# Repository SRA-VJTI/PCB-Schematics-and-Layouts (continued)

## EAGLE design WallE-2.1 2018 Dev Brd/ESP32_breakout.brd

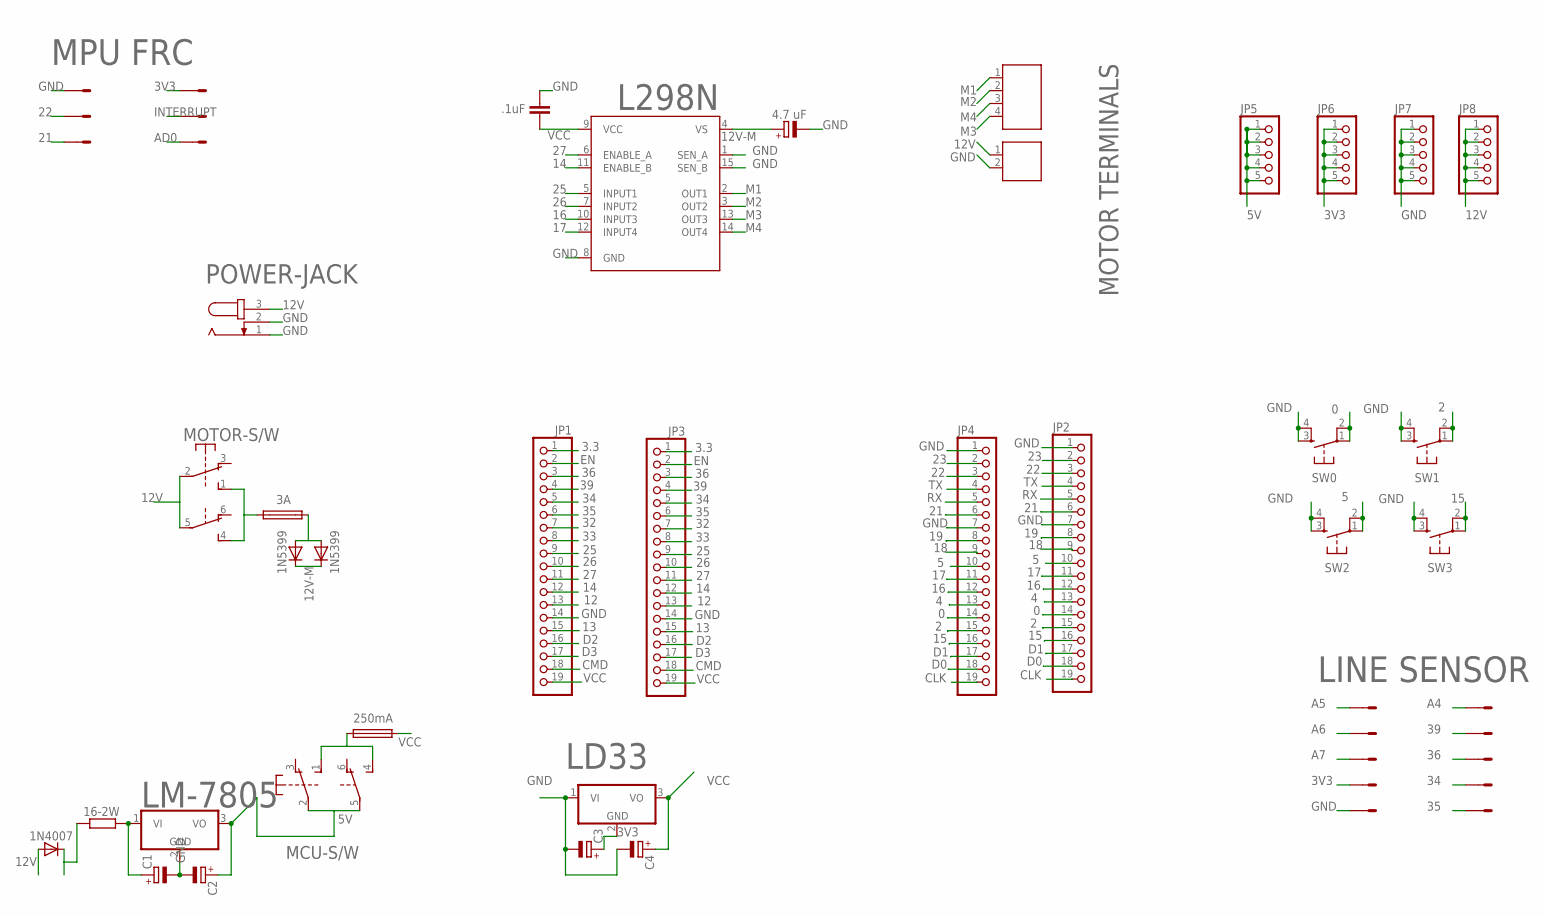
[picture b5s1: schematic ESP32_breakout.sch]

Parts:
12V: 691131710002
16-2W: R-EU_0617/17; 0617/17
C1, C2, C3, C4: CPOL-EUE2.5-6; E2,5-6
C8: 4.7 uF; E2,5-6
C9: .1uF; C5B2.5
D4: 1N4007; D-7.5
D6, D7: 1N5399; DO15-12
F1: 3A; SH25
F2: 250mA; SH25
J1: 691131710004
JP1, JP2, JP3, JP4: PINHD-1X19; 1X19
JP5, JP6, JP7, JP8: PINHD-1X5; 1X05
L298N: L298; MULTIWATT-15
LD33: 786TV; TO220V
LINE-SENSOR: 057-010-1
LM-7805: 786TV; TO220V
MCU-S/W: 9077-2
MOTOR-S/W: 9077-2
MPU-6050: 057-006-1
POWER-JACK: JACK-PLUG1; SPC4078
SW0, SW1, SW2, SW3: DTS-6

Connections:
0: JP2.14, JP4.14, SW0.1, SW0.2
2: JP2.15, JP4.15, SW1.1, SW1.2
3.3: JP1.1, JP3.1
3V3: C3.+, JP6.1, JP6.2, JP6.3, JP6.4, JP6.5, LD33.2 (GND), LINE-SENSOR.7, MPU-6050.2
4: JP2.13, JP4.13
5: JP2.10, JP4.10, SW2.1, SW2.2
5V: C2.+, JP5.1, JP5.2, JP5.3, JP5.4, JP5.5, LM-7805.3 (VO), MCU-S/W.2, MCU-S/W.5
12: JP1.13, JP3.13
12V: 12V.1, D4.A, JP8.1, JP8.2, JP8.3, JP8.4, JP8.5, MOTOR-S/W.2, MOTOR-S/W.5, POWER-JACK.3
12V-M: C8.+, D6.C, D7.C, L298N.4 (VS)
13: JP1.15, JP3.15
14: JP1.12, JP3.12, L298N.11 (ENABLE_B)
15: JP2.16, JP4.16, SW3.1, SW3.2
16: JP2.12, JP4.12, L298N.10 (INPUT3)
17: JP2.11, JP4.11, L298N.12 (INPUT4)
18: JP2.9, JP4.9
19: JP2.8, JP4.8
21: JP2.6, JP4.6, MPU-6050.5
22: JP2.3, JP4.3, MPU-6050.3
23: JP2.2, JP4.2
25: JP1.9, JP3.9, L298N.5 (INPUT1)
26: JP1.10, JP3.10, L298N.7 (INPUT2)
27: JP1.11, JP3.11, L298N.6 (ENABLE_A)
32: JP1.7, JP3.7
33: JP1.8, JP3.8
34: JP1.5, JP3.5, LINE-SENSOR.8
35: JP1.6, JP3.6, LINE-SENSOR.10
36: JP1.3, JP3.3, LINE-SENSOR.6
39: JP1.4, JP3.4, LINE-SENSOR.4
A4: LINE-SENSOR.2
A5: LINE-SENSOR.1
A6: LINE-SENSOR.3
A7: LINE-SENSOR.5
CLK: JP2.19, JP4.19
CMD: JP1.18, JP3.18
D0: JP2.18, JP4.18
D1: JP2.17, JP4.17
D2: JP1.16, JP3.16
D3: JP1.17, JP3.17
EN: JP1.2, JP3.2
GND: 12V.2, C1.-, C2.-, C3.-, C4.-, C8.-, C9.2, JP1.14, JP2.1, JP2.7, JP3.14, JP4.1, JP4.7, JP7.1, JP7.2, JP7.3, JP7.4, JP7.5, L298N.1 (SEN_A), L298N.8 (GND), L298N.15 (SEN_B), LD33.1 (VI), LINE-SENSOR.9, LM-7805.2 (GND), MPU-6050.1, MPU-6050.6, POWER-JACK.1, POWER-JACK.2, SW0.3, SW0.4, SW1.3, SW1.4, SW2.3, SW2.4, SW3.3, SW3.4
INTERRUPT: MPU-6050.4
M1: J1.1, L298N.2 (OUT1)
M2: J1.2, L298N.3 (OUT2)
M3: J1.4, L298N.13 (OUT3)
M4: J1.3, L298N.14 (OUT4)
unnamed: 16-2W.2, C1.+, LM-7805.1 (VI)
unnamed: F1.1, MOTOR-S/W.1 (S), MOTOR-S/W.4 (S)
unnamed: F2.1, MCU-S/W.1 (S), MCU-S/W.4 (S)
unnamed: 16-2W.1, D4.C
unnamed: D6.A, D7.A, F1.2
RX: JP2.5, JP4.5
TX: JP2.4, JP4.4
VCC: C4.+, C9.1, F2.2, JP1.19, JP3.19, L298N.9 (VCC), LD33.3 (VO)

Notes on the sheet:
LINE SENSOR
MOTOR TERMINALS
MPU FRC
AD0

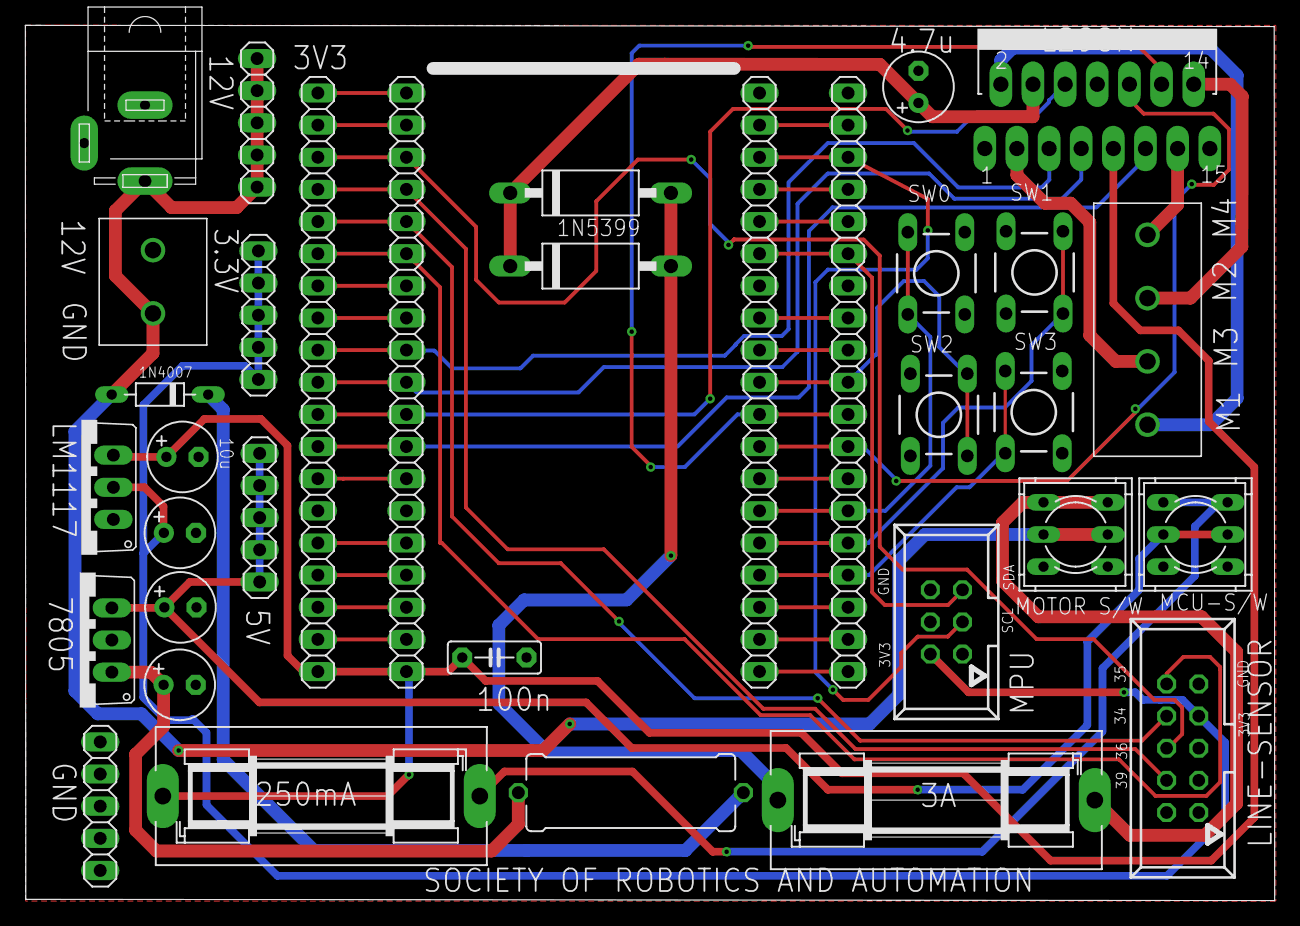
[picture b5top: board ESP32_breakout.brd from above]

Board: 2 copper layers, 98.7 x 69.2 mm, 34 parts (0 on the bottom side), 49 nets.

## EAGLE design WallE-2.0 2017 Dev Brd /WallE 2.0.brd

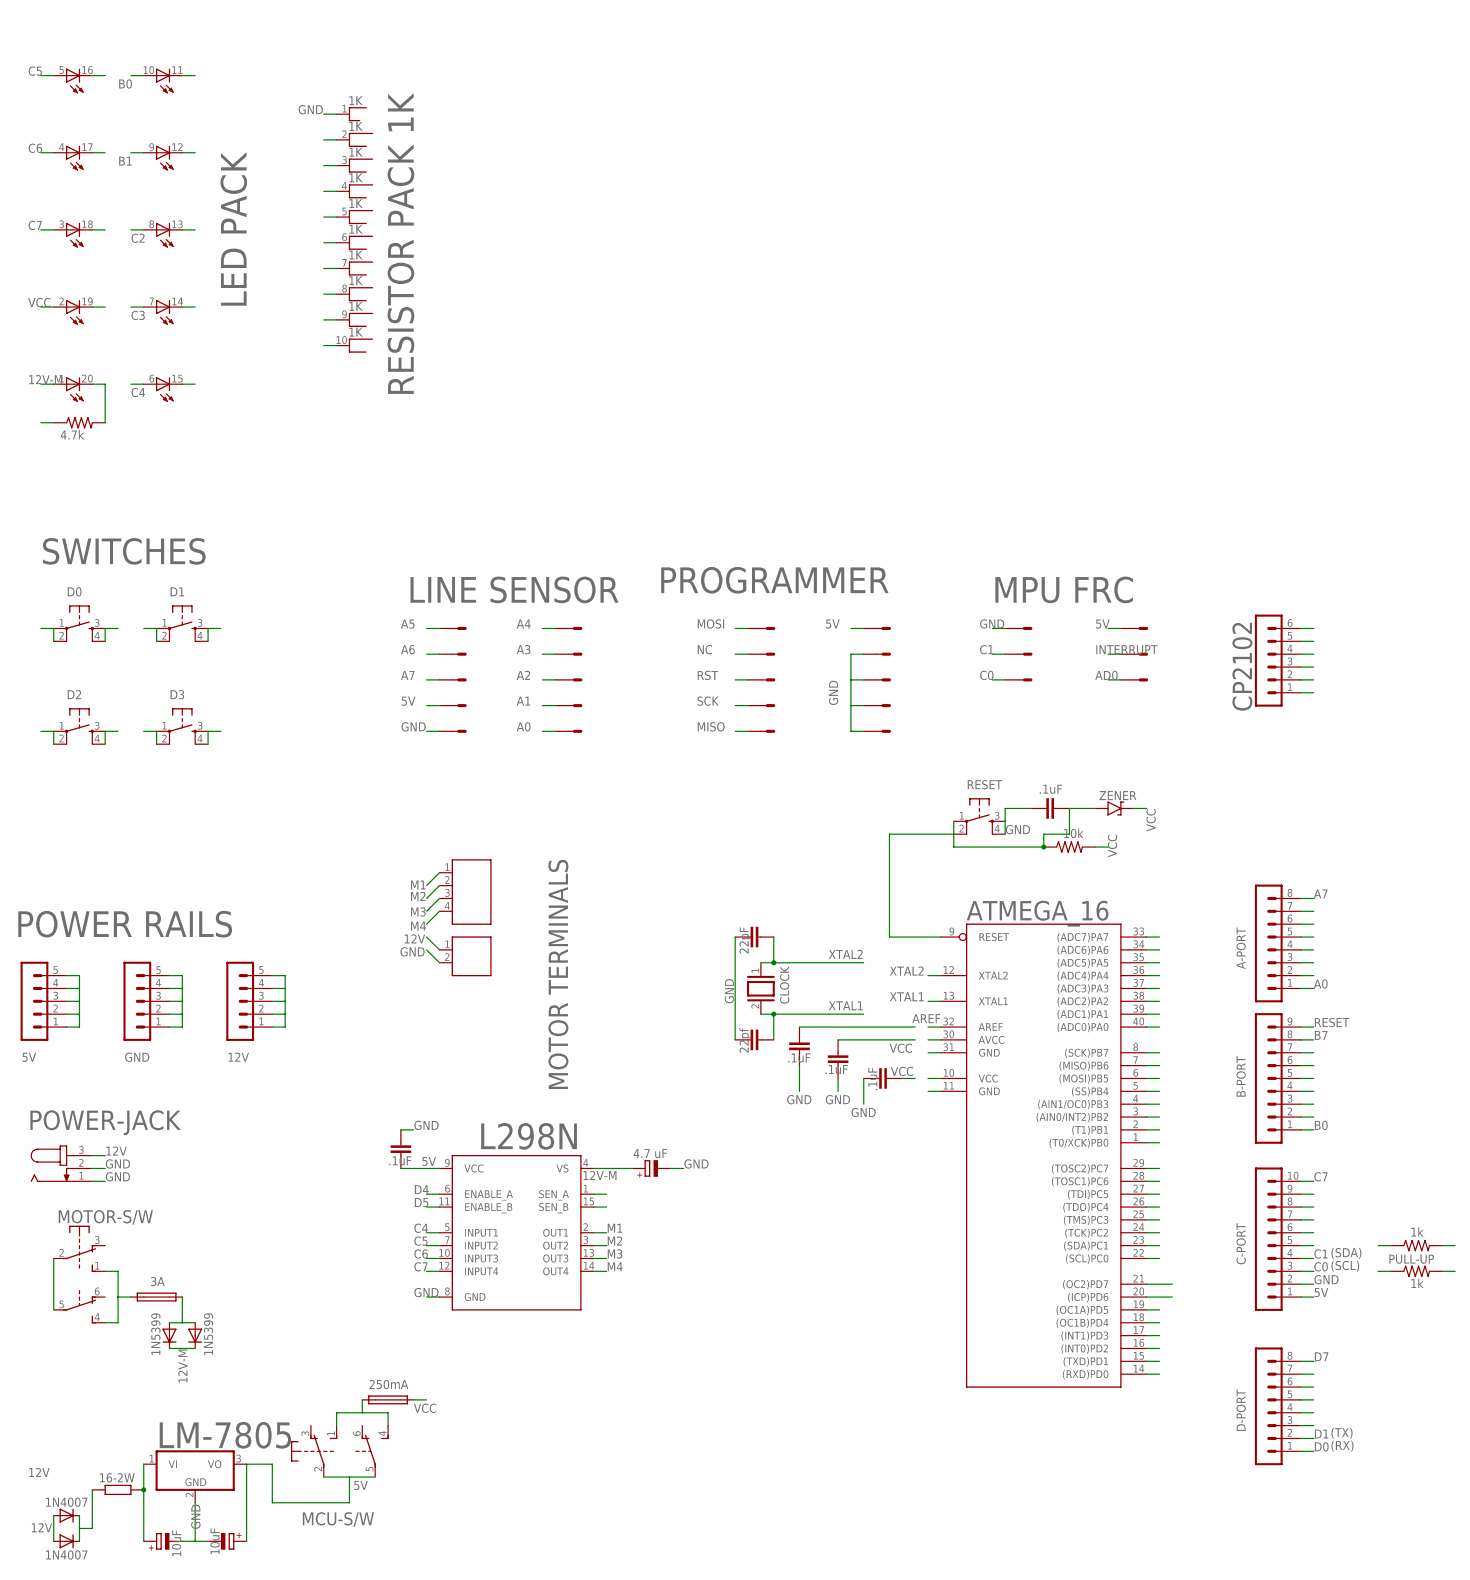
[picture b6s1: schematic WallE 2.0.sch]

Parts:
5V, 12V: MA05-1
16-2W: R-EU_0617/17; 0617/17
A-PORT: MA08-1
ATMEGA_16: MEGA32-P; DIL40
B-PORT: MA09-1
C1, C10: 10uF; E2,5-6
C2, C5, C6, C7, C9: .1uF; C5B2.5
C3: 22pf; C2.5-2
C4: 22pF; C2.5-2
C8: 4.7 uF; E2,5-6
C-PORT: MA10-1
CLOCK: XTAL/S; QS
CP2102: MA06-1
D0, D1, D2, D3: DTS-6
D4, D5: 1N4007; D-7.5
D6, D7: 1N5399; DO15-12
D-PORT: MA08-1
DZ1: LB10
F1: 3A; SH25
F2: 250mA; SH25
GND: MA05-1
J1: 691131710004
J2: 691131710002
L298N: L298; MULTIWATT-15
LINE-SENSOR: 057-010-1
LM-7805: 786TV; TO220V
MCU-S/W: 9077-2
MOTOR-S/W: 9077-2
MPU-6050: 057-006-1
POWER-JACK: JACK-PLUG1; SPC4078
R2: 4.7k; 0207/7
R3: 10k; 0207/7
R5, R6: 1k; 0207/7
RESET: DTS-6
RN1: 1K; RN-10
X2: PROGRAMMER; 057-010-1
ZENER: ZENER; DO35-2

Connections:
3.3V: CP2102.1
5V: 5V.1, 5V.2, 5V.3, 5V.4, 5V.5, C9.1, C10.+, C-PORT.1, CP2102.6, L298N.9 (VCC), LINE-SENSOR.7, LM-7805.3 (VO), MCU-S/W.2, MCU-S/W.5, MPU-6050.2, R5.2, R6.2, X2.2
12V: 12V.1, 12V.2, 12V.3, 12V.4, 12V.5, D4.A, D5.A, J2.1, MOTOR-S/W.2, MOTOR-S/W.5, POWER-JACK.3
12V-M: C8.+, D6.C, D7.C, DZ1.1 (A), L298N.4 (VS)
A0: A-PORT.1, ATMEGA_16.40 ((ADC0)PA0), LINE-SENSOR.10
A1: A-PORT.2, ATMEGA_16.39 ((ADC1)PA1), LINE-SENSOR.8
A2: A-PORT.3, ATMEGA_16.38 ((ADC2)PA2), LINE-SENSOR.6
A3: A-PORT.4, ATMEGA_16.37 ((ADC3)PA3), LINE-SENSOR.4
A4: A-PORT.5, ATMEGA_16.36 ((ADC4)PA4), LINE-SENSOR.2
A5: A-PORT.6, ATMEGA_16.35 ((ADC5)PA5), LINE-SENSOR.1
A6: A-PORT.7, ATMEGA_16.34 ((ADC6)PA6), LINE-SENSOR.3
A7: A-PORT.8, ATMEGA_16.33 ((ADC7)PA7), LINE-SENSOR.5
AREF: ATMEGA_16.32 (AREF), C7.1
B0: ATMEGA_16.1 ((T0/XCK)PB0), B-PORT.1, DZ1.10 (A)
B0R: DZ1.11 (C), RN1.10
B1: ATMEGA_16.2 ((T1)PB1), B-PORT.2, DZ1.9 (A)
B1R: DZ1.12 (C), RN1.9
B2: ATMEGA_16.3 ((AIN0/INT2)PB2), B-PORT.3
B3: ATMEGA_16.4 ((AIN1/OC0)PB3), B-PORT.4
B4: ATMEGA_16.5 ((SS)PB4), B-PORT.5
B5: ATMEGA_16.6 ((MOSI)PB5), B-PORT.6, X2.1
B6: ATMEGA_16.7 ((MISO)PB6), B-PORT.7, X2.9
B7: ATMEGA_16.8 ((SCK)PB7), B-PORT.8, X2.7
C0: ATMEGA_16.22 ((SCL)PC0), C-PORT.3, MPU-6050.5, R6.1
C1: ATMEGA_16.23 ((SDA)PC1), C-PORT.4, MPU-6050.3, R5.1
C2: ATMEGA_16.24 ((TCK)PC2), C-PORT.5, DZ1.8 (A)
C2R: DZ1.13 (C), RN1.8
C3: ATMEGA_16.25 ((TMS)PC3), C-PORT.6, DZ1.7 (A)
C3R: DZ1.14 (C), RN1.7
C4: ATMEGA_16.26 ((TDO)PC4), C-PORT.7, DZ1.6 (A), L298N.5 (INPUT1)
C4R: DZ1.15 (C), RN1.6
C5: ATMEGA_16.27 ((TDI)PC5), C-PORT.8, DZ1.5 (A), L298N.7 (INPUT2)
C5R: DZ1.16 (C), RN1.5
C6: ATMEGA_16.28 ((TOSC1)PC6), C-PORT.9, DZ1.4 (A), L298N.10 (INPUT3)
C6R: DZ1.17 (C), RN1.4
C7: ATMEGA_16.29 ((TOSC2)PC7), C-PORT.10, DZ1.3 (A), L298N.12 (INPUT4)
C7R: DZ1.18 (C), RN1.3
D0: ATMEGA_16.14 ((RXD)PD0), CP2102.3, D0.1, D0.2, D-PORT.1
D1: ATMEGA_16.15 ((TXD)PD1), CP2102.4, D1.1, D1.2, D-PORT.2
D2: ATMEGA_16.16 ((INT0)PD2), D2.1, D2.2, D-PORT.3
D3: ATMEGA_16.17 ((INT1)PD3), D3.1, D3.2, D-PORT.4
D4: ATMEGA_16.18 ((OC1B)PD4), D-PORT.5, L298N.6 (ENABLE_A)
D5: ATMEGA_16.19 ((OC1A)PD5), D-PORT.6, L298N.11 (ENABLE_B)
D6: ATMEGA_16.20 ((ICP)PD6), D-PORT.7
D7: ATMEGA_16.21 ((OC2)PD7), D-PORT.8
DTR: CP2102.2
GND: ATMEGA_16.11 (GND), ATMEGA_16.31 (GND), C1.-, C2.2, C3.2, C4.2, C5.2, C6.2, C7.2, C8.-, C9.2, C10.-, C-PORT.2, CP2102.5, D0.3, D0.4, D1.3, D1.4, D2.3, D2.4, D3.3, D3.4, GND.1, GND.2, GND.3, GND.4, GND.5, J2.2, L298N.1 (SEN_A), L298N.8 (GND), L298N.15 (SEN_B), LINE-SENSOR.9, LM-7805.2 (GND), MPU-6050.1, MPU-6050.6, POWER-JACK.1, POWER-JACK.2, R2.1, RESET.3, RESET.4, RN1.1, X2.4, X2.6, X2.8, X2.10
INTERRUPT: MPU-6050.4
M1: J1.1, L298N.2 (OUT1)
M2: J1.2, L298N.3 (OUT2)
M3: J1.3, L298N.13 (OUT3)
M4: J1.4, L298N.14 (OUT4)
unnamed: DZ1.20 (C), R2.2
unnamed: 16-2W.2, C1.+, LM-7805.1 (VI)
unnamed: F1.1, MOTOR-S/W.1 (S), MOTOR-S/W.4 (S)
unnamed: F2.1, MCU-S/W.1 (S), MCU-S/W.4 (S)
unnamed: 16-2W.1, D4.C, D5.C
unnamed: D6.A, D7.A, F1.2
RESET: ATMEGA_16.9 (RESET), B-PORT.9, C5.1, R3.1, RESET.1, RESET.2, X2.5, ZENER.A
VCC: ATMEGA_16.10 (VCC), ATMEGA_16.30 (AVCC), C2.1, C6.1, DZ1.2 (A), F2.2, R3.2, ZENER.C
VCCR: DZ1.19 (C), RN1.2
XTAL1: ATMEGA_16.13 (XTAL1), C3.1, CLOCK.2
XTAL2: ATMEGA_16.12 (XTAL2), C4.1, CLOCK.1

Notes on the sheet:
MOSI
RST
SCK
MISO
GND
SWITCHES
POWER RAILS
LINE SENSOR
RESISTOR PACK 1K
LED PACK
MPU FRC
(SDA)
(SCL)
PULL-UP
MOTOR TERMINALS
(TX)
(RX)
AD0

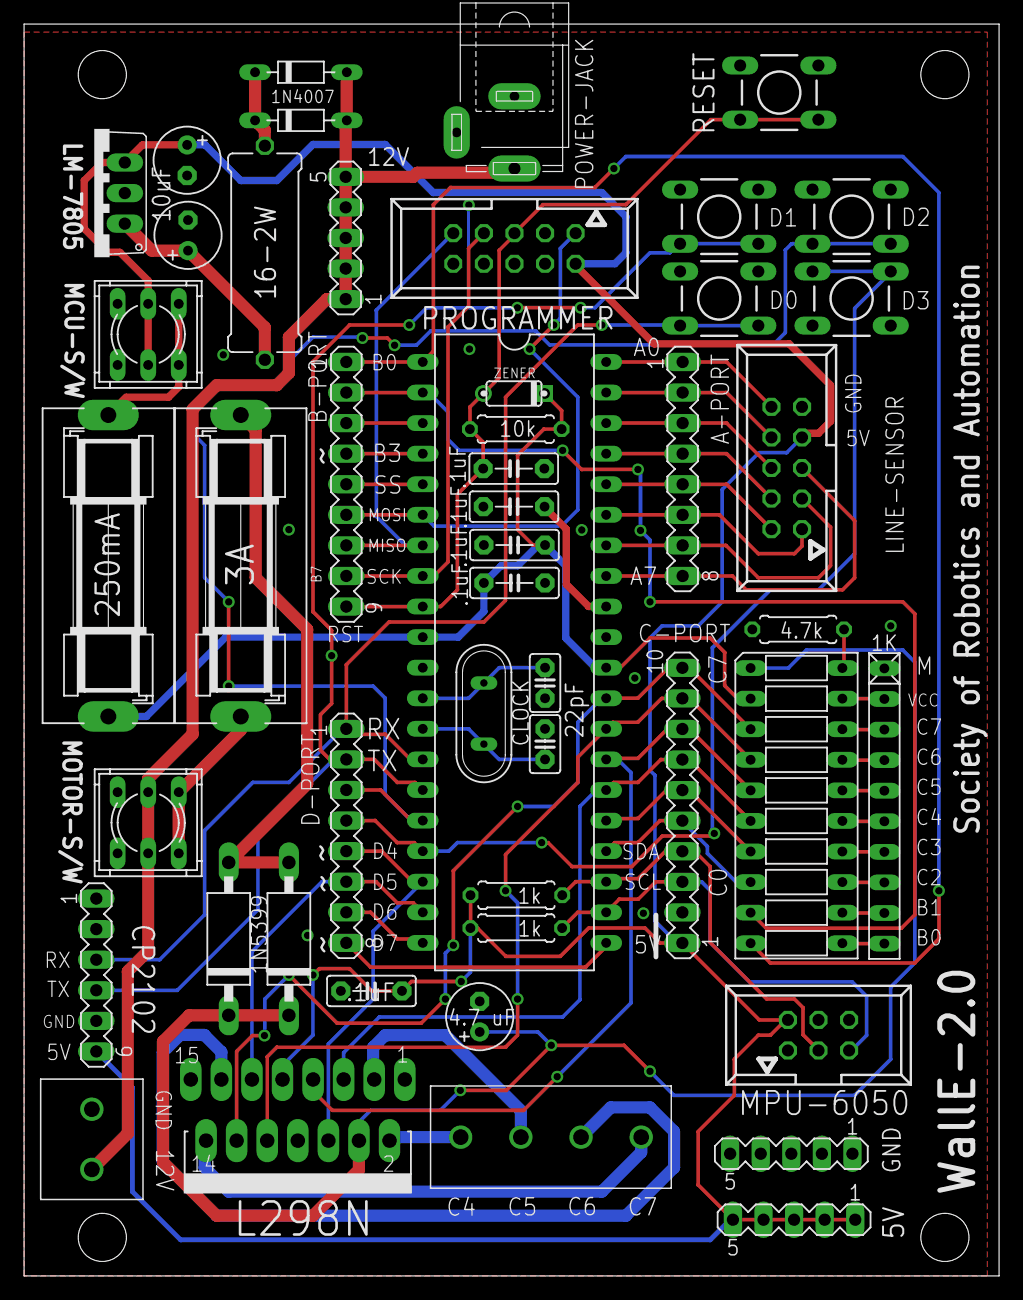
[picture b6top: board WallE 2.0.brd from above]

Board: 2 copper layers, 81.0 x 104.0 mm, 49 parts (0 on the bottom side), 60 nets.

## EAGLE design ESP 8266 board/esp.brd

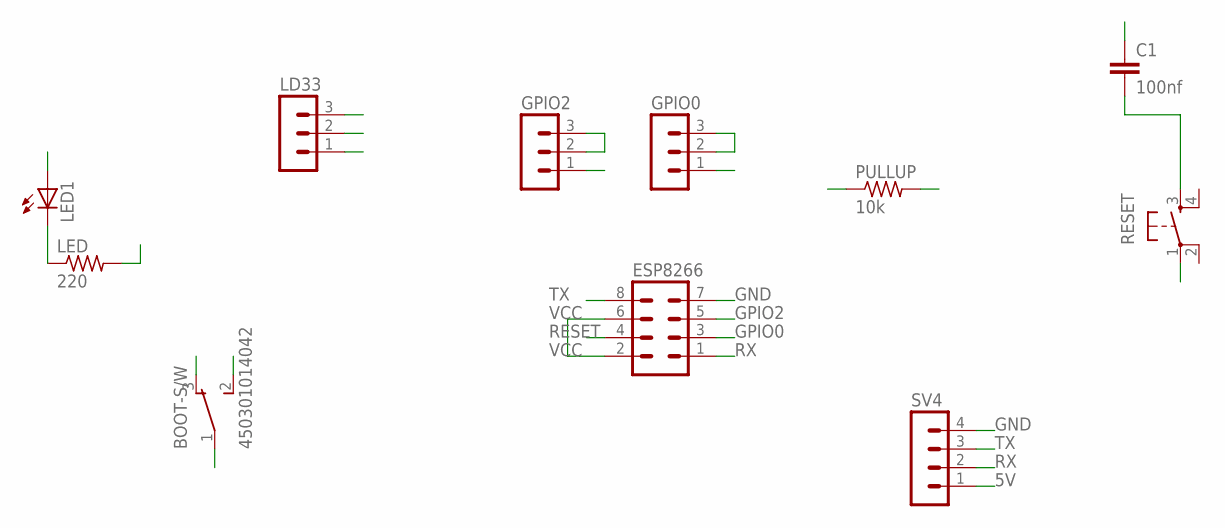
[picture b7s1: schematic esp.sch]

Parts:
BOOT-S/W: 450301014042
C1: 100nf; C025-024X044
ESP8266: MA04-2
GPIO0, GPIO2: MA03-1
LD33: MA03-1
LED: 220; 0204/5
LED1: LED_ELD260; LED_LD260
PULLUP: 10k; 0204/5
RESET: DTS-6
SV4: MA04-1

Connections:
5V: LD33.1, SV4.1
GND: BOOT-S/W.3, ESP8266.7, GPIO0.1, GPIO2.1, LD33.2, LED.2, RESET.1, SV4.4
GPIO0: BOOT-S/W.1, ESP8266.3
GPIO0--: BOOT-S/W.2, GPIO0.2, GPIO0.3
GPIO2: ESP8266.5, GPIO2.2, GPIO2.3, LED1.A
unnamed: LED.1, LED1.K (C)
unnamed: C1.2, RESET.3
RESET: C1.1, ESP8266.4, PULLUP.1
RX: ESP8266.1, SV4.2
TX: ESP8266.8, SV4.3
VCC: ESP8266.2, ESP8266.6, LD33.3, PULLUP.2

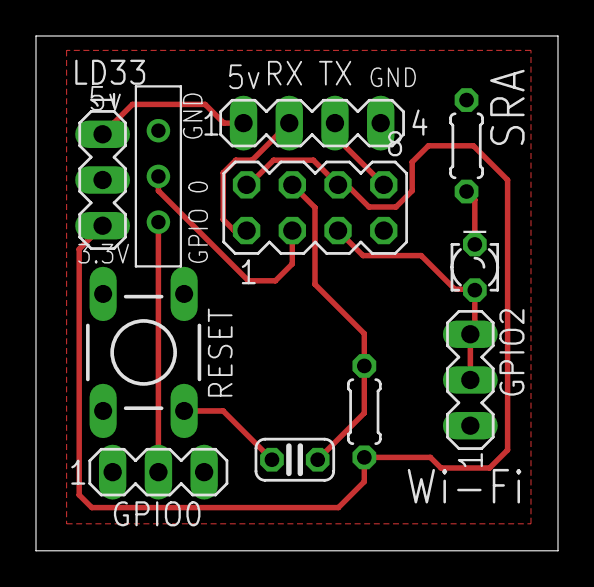
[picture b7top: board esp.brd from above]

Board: 2 copper layers, 29.0 x 28.6 mm, 11 parts (0 on the bottom side), 11 nets.

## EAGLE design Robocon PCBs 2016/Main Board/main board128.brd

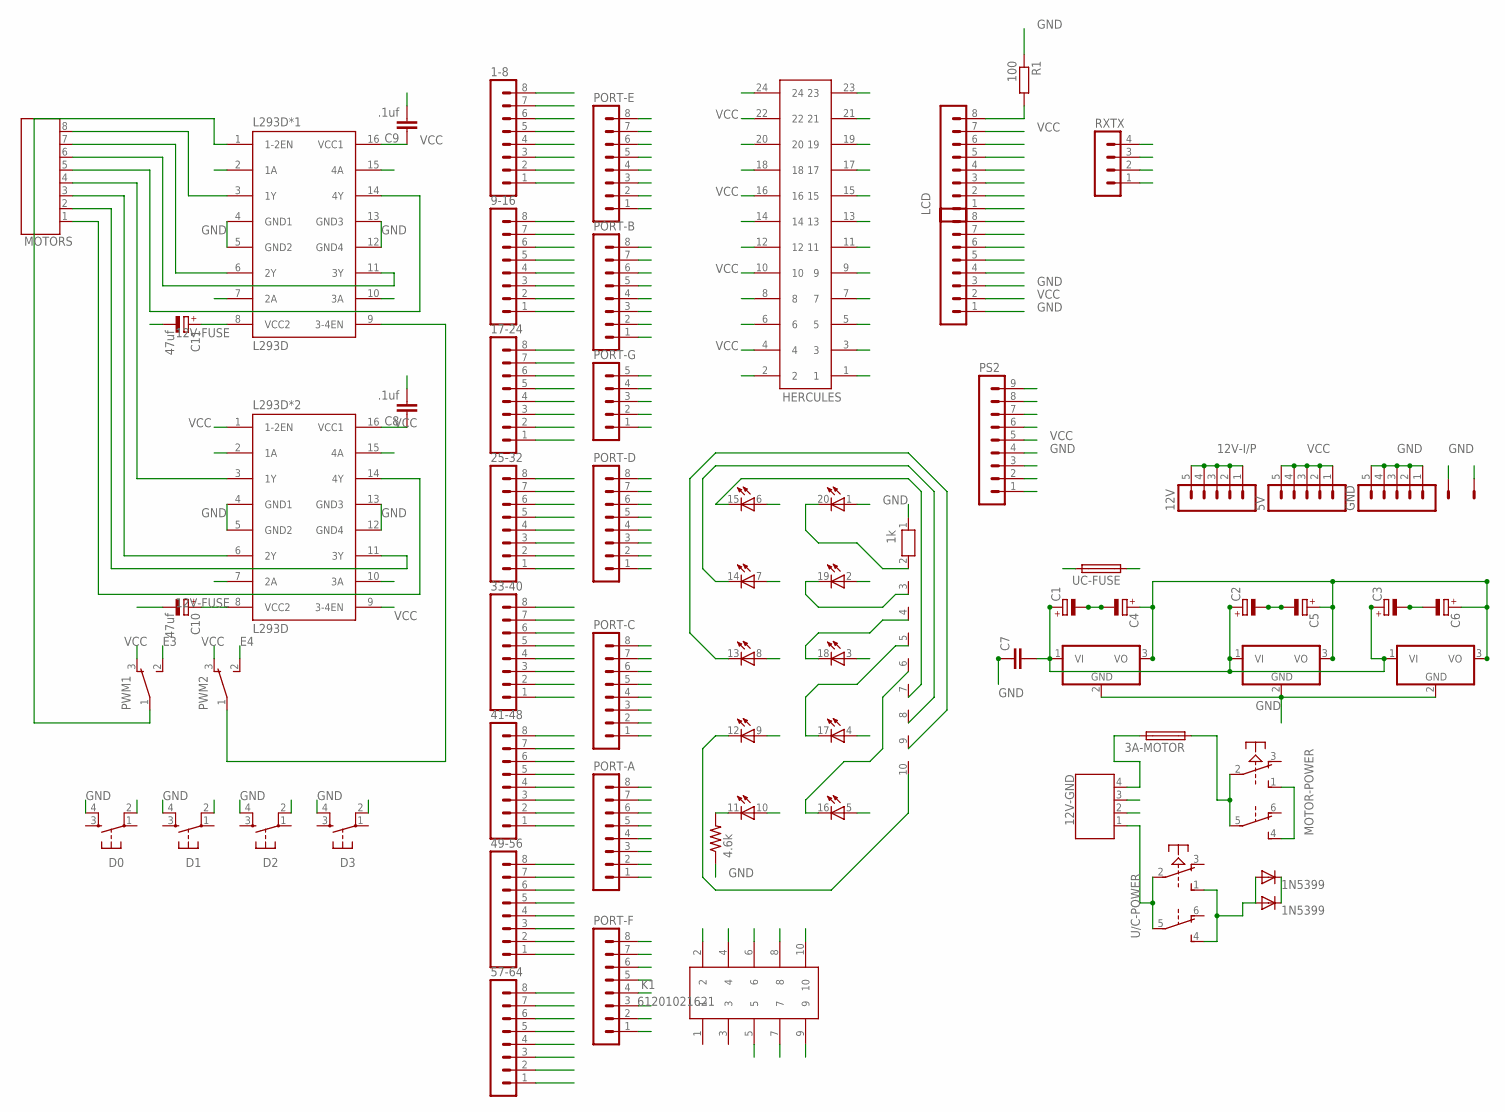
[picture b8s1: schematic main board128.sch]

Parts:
1-8, 9-16, 17-24, 25-32, 33-40, 41-48, 49-56, 57-64: MA08-1
3A-MOTOR: SH25
5V, 12V: MA05-1
12V-GND: 691131710004
7805-1, 7805-2, 7805-3: 7805T; TO220H
BASEMOTORSLED: LB10
C1, C2, C3, C4, C5, C6: CPOL-EUE2.5-5; E2,5-5
C7: C5/2.5; C5B2.5
C8, C9: .1uf; C5B2.5
C10, C11: 47uf; E2,5-5
D0, D1, D2, D3: DTS-6
GND: MA05-1
HERCULES: 61202421621
K1: 61201021621
L293D*1, L293D*2: L293D; DIL16
LCD: MA08-1
LCD*: MA08-1
MOTOR-POWER: PVA2R
MOTORS: 691131710008
PORT-A: MA08-1
PORT-B: MA08-1
PORT-C: MA08-1
PORT-D: MA08-1
PORT-E: MA08-1
PORT-F: MA08-1
PORT-G: MA05-1
POWER-D1, POWER-D2: 1N5399; DO15-12
PS2: MA09-1
PWM1, PWM2: 450301014042
R1: 100; 0204/7
R2: 4.6k; 0204/5
RN1: 1k; RN-10
RXTX: MA04-1
SENSOR-POWER: KK-156-2
U/C-POWER: PVA2R
UC-FUSE: SH25

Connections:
1: 1-8.1
12V: 7805-1.1 (VI), 7805-2.1 (VI), 7805-3.1 (VI), BASEMOTORSLED.10 (A), C1.+, C2.+, C3.+, C7.2, POWER-D1.C, POWER-D2.C
12V-FUSE: C10.+, C11.+, L293D*1.8 (VCC2), L293D*2.8 (VCC2), MOTOR-POWER.1 (S), MOTOR-POWER.4 (S)
12V-I/P: 3A-MOTOR.2, 12V.1, 12V.2, 12V.3, 12V.4, 12V.5, 12V-GND.1, 12V-GND.4, U/C-POWER.2, U/C-POWER.5
62: 57-64.6
A0: 49-56.3, LCD.3, PORT-A.1
A1: 49-56.2, LCD.4, PORT-A.2
A2: 49-56.1, LCD.5, PORT-A.3
A3: 41-48.8, LCD.6, PORT-A.4
A4: 41-48.7, PORT-A.5
A5: 41-48.6, LCD*.4, PORT-A.6
A6: 41-48.5, LCD*.5, PORT-A.7
A7: 41-48.4, LCD*.6, PORT-A.8
B0: 9-16.2, L293D*2.2 (1A), PORT-B.1
B1: 9-16.3, L293D*2.7 (2A), PORT-B.2
B2: 9-16.4, L293D*2.10 (3A), PORT-B.3
B3: 9-16.5, L293D*2.15 (4A), PORT-B.4
B4: 9-16.6, HERCULES.3, PORT-B.5
B5: 9-16.7, HERCULES.9, PORT-B.6
B6: 9-16.8, HERCULES.15, PORT-B.7
B7: 17-24.1, HERCULES.21, PORT-B.8
C0: 33-40.3, BASEMOTORSLED.1 (A), HERCULES.1, PORT-C.1
C1: 33-40.4, BASEMOTORSLED.2 (A), HERCULES.5, PORT-C.2
C2: 33-40.5, BASEMOTORSLED.3 (A), HERCULES.7, PORT-C.3
C3: 33-40.6, BASEMOTORSLED.4 (A), HERCULES.11, PORT-C.4
C4: 33-40.7, BASEMOTORSLED.5 (A), HERCULES.13, PORT-C.5
C5: 33-40.8, BASEMOTORSLED.6 (A), HERCULES.17, PORT-C.6
C6: 41-48.1, BASEMOTORSLED.7 (A), HERCULES.19, PORT-C.7
C7: 41-48.2, BASEMOTORSLED.8 (A), HERCULES.23, PORT-C.8
D0: 25-32.1, D0.2, HERCULES.2, PORT-D.1
D1: 25-32.2, D1.2, HERCULES.6, PORT-D.2
D2: 25-32.3, D2.2, HERCULES.8, PORT-D.3, RXTX.3
D3: 25-32.4, D3.2, HERCULES.12, PORT-D.4, RXTX.4
D4: 25-32.5, HERCULES.14, PORT-D.5
D5: 25-32.6, HERCULES.18, PORT-D.6
D6: 25-32.7, HERCULES.20, PORT-D.7
D7: 25-32.8, HERCULES.24, PORT-D.8
E0: 1-8.2, L293D*1.2 (1A), PORT-E.1, RXTX.1
E1: 1-8.3, L293D*1.7 (2A), PORT-E.2, RXTX.2
E2: 1-8.4, PORT-E.3
E3: 1-8.5, PORT-E.4, PWM1.2
E4: 1-8.6, PORT-E.5, PWM2.2
E5: 1-8.7, PORT-E.6
E6: 1-8.8, L293D*1.10 (3A), PORT-E.7
E7: 9-16.1, L293D*1.15 (4A), PORT-E.8
F0: 57-64.5, K1.2, PORT-F.1
F1: 57-64.4, K1.4, PORT-F.2
F2: 57-64.3, K1.6, PORT-F.3
F3: 57-64.2, K1.8, PORT-F.4
F4: 57-64.1, K1.10, PORT-F.5
F5: 49-56.8, K1.9, PORT-F.6
F6: 49-56.7, K1.7, PORT-F.7
F7: 49-56.6, K1.5, PORT-F.8
FUSE-M/C: 7805-1.3 (VO), 7805-2.3 (VO), 7805-3.3 (VO), C4.+, C5.+, C6.+, UC-FUSE.1
G0: 33-40.1, PORT-G.1, PS2.1
G1: 33-40.2, PORT-G.2, PS2.2
G2: 41-48.3, PORT-G.3, PS2.6
G3: 17-24.2, PORT-G.4, PS2.7
G4: 17-24.3, PORT-G.5
GND: 12V-GND.2, 12V-GND.3, 17-24.6, 49-56.5, 57-64.7, 7805-1.2 (GND), 7805-2.2 (GND), 7805-3.2 (GND), C1.-, C2.-, C3.-, C4.-, C5.-, C6.-, C7.1, C8.2, C9.2, C10.-, C11.-, D0.4, D1.4, D2.4, D3.4, GND.1, GND.2, GND.3, GND.4, GND.5, L293D*1.4 (GND1), L293D*1.5 (GND2), L293D*1.12 (GND4), L293D*1.13 (GND3), L293D*2.4 (GND1), L293D*2.5 (GND2), L293D*2.12 (GND4), L293D*2.13 (GND3), LCD*.1, LCD*.3, PS2.4, R1.1, R2.1, RN1.1, SENSOR-POWER.2
L293D-2: L293D*2.14 (4Y), MOTORS.1
MOTORSWITCH: 3A-MOTOR.1, MOTOR-POWER.2, MOTOR-POWER.5
unnamed: L293D*1.9 (3-4EN), PWM2.1
unnamed: POWER-D1.A, POWER-D2.A, U/C-POWER.1 (S), U/C-POWER.4 (S)
unnamed: L293D*1.6 (2Y), MOTORS.7
unnamed: L293D*1.3 (1Y), MOTORS.8
unnamed: L293D*1.14 (4Y), MOTORS.5
unnamed: L293D*1.11 (3Y), MOTORS.6
unnamed: L293D*2.11 (3Y), MOTORS.2
unnamed: L293D*2.6 (2Y), MOTORS.3
unnamed: L293D*2.3 (1Y), MOTORS.4
unnamed: L293D*1.1 (1-2EN), PWM1.1
unnamed: BASEMOTORSLED.12 (C), RN1.10
unnamed: BASEMOTORSLED.11 (C), R2.2
NC: LCD*.7
NC*: LCD*.8
NC**: LCD.1
NC***: LCD.2
RC0: BASEMOTORSLED.20 (C), RN1.2
RC1: BASEMOTORSLED.19 (C), RN1.3
RC2: BASEMOTORSLED.18 (C), RN1.4
RC3: BASEMOTORSLED.17 (C), RN1.5
RC4: BASEMOTORSLED.16 (C), RN1.6
RC5: BASEMOTORSLED.15 (C), RN1.7
RC6: BASEMOTORSLED.14 (C), RN1.8
RC7: BASEMOTORSLED.13 (C), RN1.9
RESET: 17-24.4
VCC: 5V.1, 5V.2, 5V.3, 5V.4, 5V.5, 17-24.5, 49-56.4, 57-64.8, BASEMOTORSLED.9 (A), C8.1, C9.1, HERCULES.4, HERCULES.10, HERCULES.16, HERCULES.22, L293D*1.16 (VCC1), L293D*2.1 (1-2EN), L293D*2.9 (3-4EN), L293D*2.16 (VCC1), LCD.7, LCD*.2, PS2.5, PWM1.3, PWM2.3, SENSOR-POWER.1, UC-FUSE.2
XTAL1: 17-24.8
XTAL2: 17-24.7
XTAL3: LCD.8, R1.2

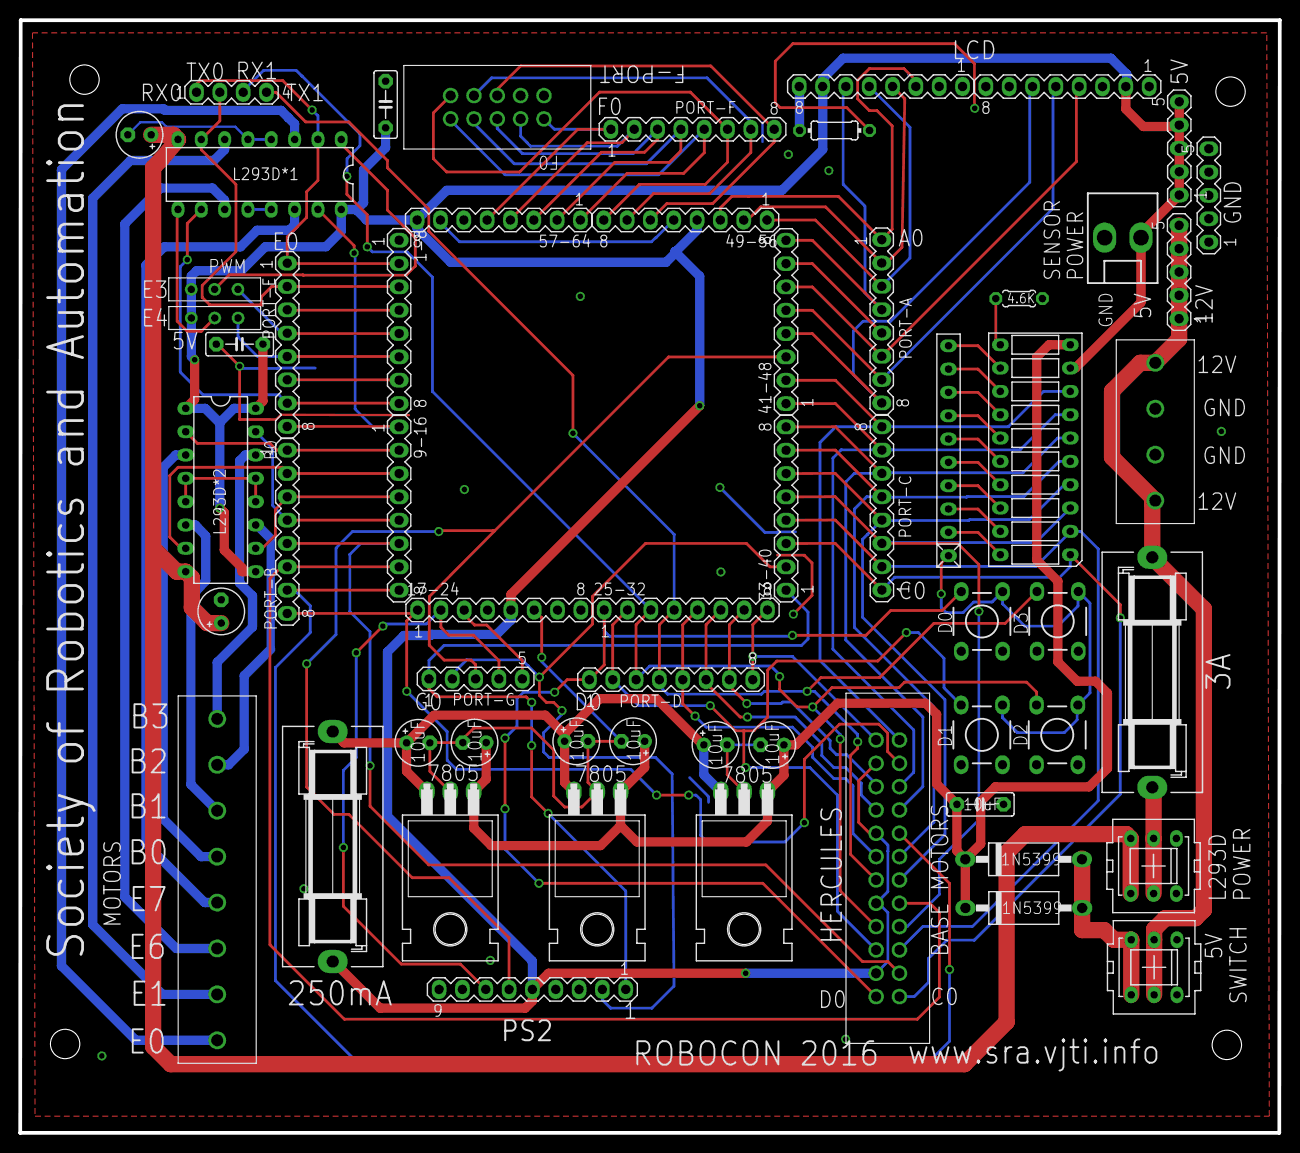
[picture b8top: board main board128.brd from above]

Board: 2 copper layers, 137.2 x 121.1 mm, 59 parts (0 on the bottom side), 82 nets.

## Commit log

2020-02-05 Add Gitignore File
2020-02-05 Add PCB files for Robocon 2016
2020-02-05 Add PCB files for WallE Workshop - 2016
2020-02-05 Add PCB files for MPU breakout board for WallE 2.0 Workshop
2020-02-05 Add PCB files for ESP8266 breakout for IOT Workshop 2016
2020-02-05 Add MIT License
2020-02-16 Add PCB files for WallE 2.0 Workshop
2020-02-16 Add PCB files for WallE 2.1 Workshop on ESP32
2020-02-16 Add PCB files for Robocon 2017
